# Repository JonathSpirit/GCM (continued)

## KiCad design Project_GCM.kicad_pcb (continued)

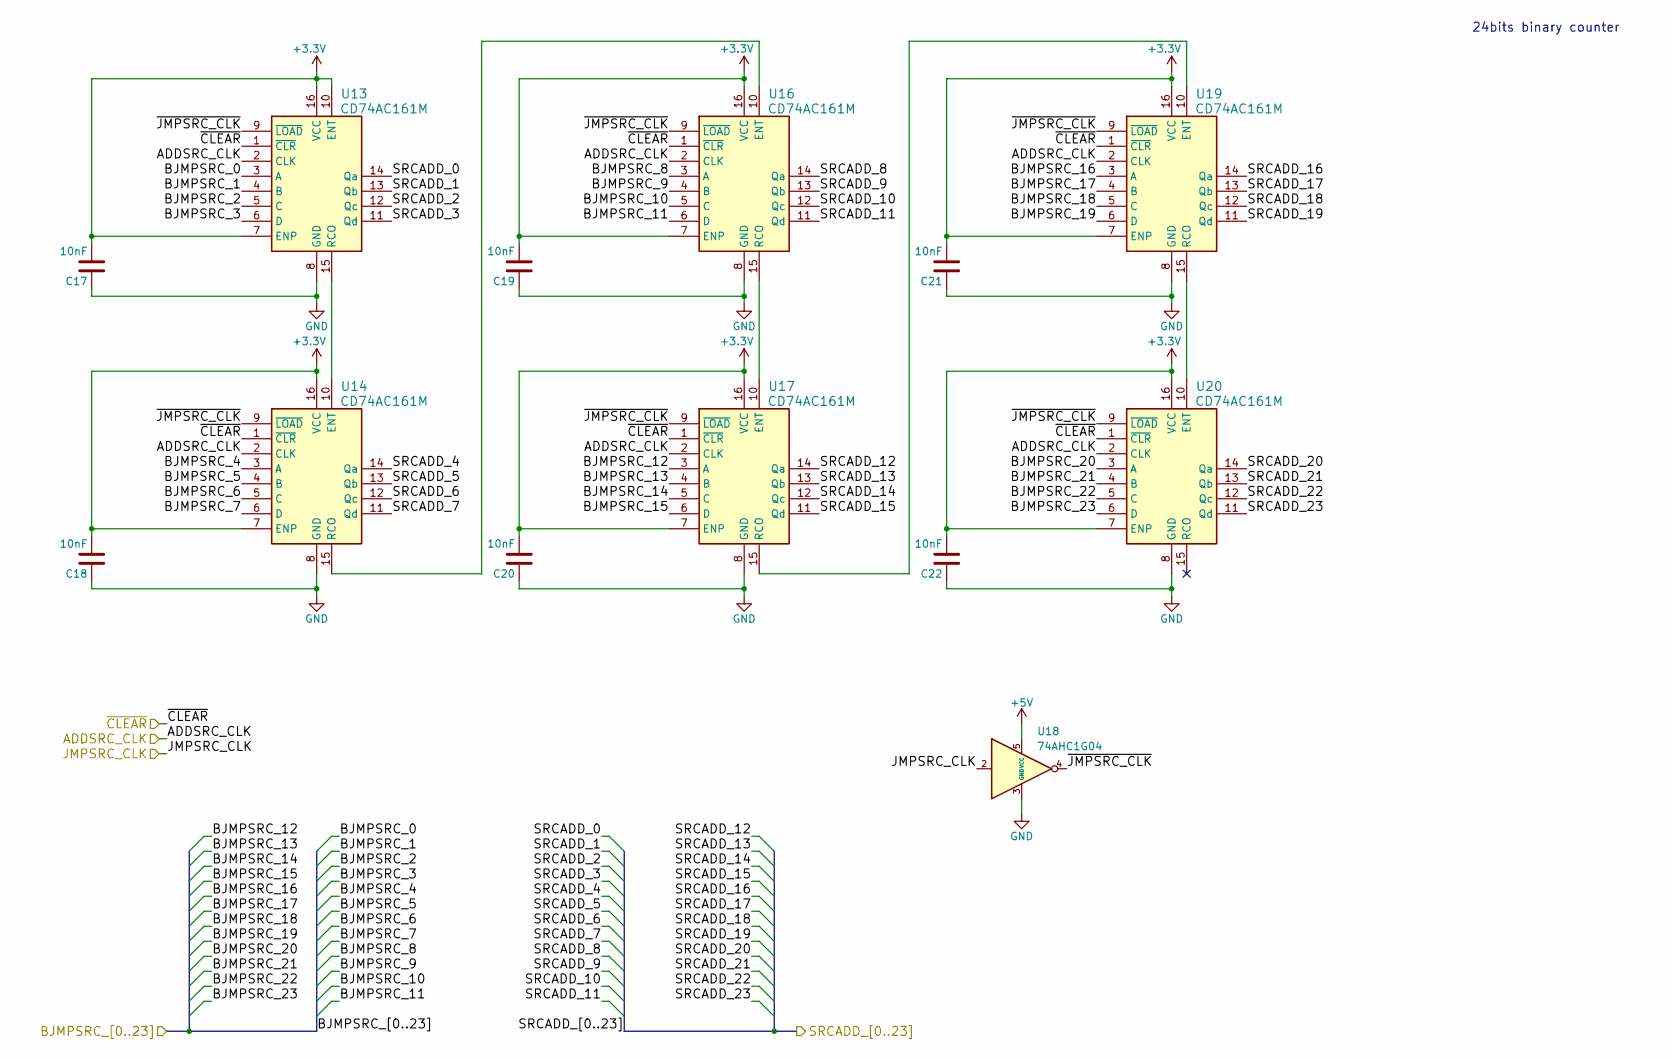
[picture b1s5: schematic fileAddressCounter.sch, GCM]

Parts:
C17, C18, C19, C20, C21, C22: 10nF; C_0805_2012Metric
U13, U14, U16, U17, U19, U20: CD74AC161M; SOP-16_3.9x9.9mm_P1.27mm
U18: 74AHC1G04; SOT-23-5

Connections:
+5V: U18.5 (VCC); also elsewhere on the board
/ADDSRC_CLK: U13.2 (CLK), U14.2 (CLK), U16.2 (CLK), U17.2 (CLK), U19.2 (CLK), U20.2 (CLK); also elsewhere on the board
/AddressCounter/BJMPSRC_0: U13.3 (A); also elsewhere on the board
/AddressCounter/BJMPSRC_1: U13.4 (B); also elsewhere on the board
/AddressCounter/BJMPSRC_2: U13.5 (C); also elsewhere on the board
/AddressCounter/BJMPSRC_3: U13.6 (D); also elsewhere on the board
/AddressCounter/BJMPSRC_4: U14.3 (A); also elsewhere on the board
/AddressCounter/BJMPSRC_5: U14.4 (B); also elsewhere on the board
/AddressCounter/BJMPSRC_6: U14.5 (C); also elsewhere on the board
/AddressCounter/BJMPSRC_7: U14.6 (D); also elsewhere on the board
/AddressCounter/BJMPSRC_8: U16.3 (A); also elsewhere on the board
/AddressCounter/BJMPSRC_9: U16.4 (B); also elsewhere on the board
/AddressCounter/BJMPSRC_10: U16.5 (C); also elsewhere on the board
/AddressCounter/BJMPSRC_11: U16.6 (D); also elsewhere on the board
/AddressCounter/BJMPSRC_12: U17.3 (A); also elsewhere on the board
/AddressCounter/BJMPSRC_13: U17.4 (B); also elsewhere on the board
/AddressCounter/BJMPSRC_14: U17.5 (C); also elsewhere on the board
/AddressCounter/BJMPSRC_15: U17.6 (D); also elsewhere on the board
/AddressCounter/BJMPSRC_16: U19.3 (A); also elsewhere on the board
/AddressCounter/BJMPSRC_17: U19.4 (B); also elsewhere on the board
/AddressCounter/BJMPSRC_18: U19.5 (C); also elsewhere on the board
/AddressCounter/BJMPSRC_19: U19.6 (D); also elsewhere on the board
/AddressCounter/BJMPSRC_20: U20.3 (A); also elsewhere on the board
/AddressCounter/BJMPSRC_21: U20.4 (B); also elsewhere on the board
/AddressCounter/BJMPSRC_22: U20.5 (C); also elsewhere on the board
/AddressCounter/BJMPSRC_23: U20.6 (D); also elsewhere on the board
/AddressCounter/~JMPSRC_CLK: U13.9 (~LOAD), U14.9 (~LOAD), U16.9 (~LOAD), U17.9 (~LOAD), U18.4, U19.9 (~LOAD), U20.9 (~LOAD)
/JMPSRC_CLK: U18.2; also elsewhere on the board
/SRCADD_0: U13.14 (Qa); also elsewhere on the board
/SRCADD_1: U13.13 (Qb); also elsewhere on the board
/SRCADD_2: U13.12 (Qc); also elsewhere on the board
/SRCADD_3: U13.11 (Qd); also elsewhere on the board
/SRCADD_4: U14.14 (Qa); also elsewhere on the board
/SRCADD_5: U14.13 (Qb); also elsewhere on the board
/SRCADD_6: U14.12 (Qc); also elsewhere on the board
/SRCADD_7: U14.11 (Qd); also elsewhere on the board
/SRCADD_8: U16.14 (Qa); also elsewhere on the board
/SRCADD_9: U16.13 (Qb); also elsewhere on the board
/SRCADD_10: U16.12 (Qc); also elsewhere on the board
/SRCADD_11: U16.11 (Qd); also elsewhere on the board
/SRCADD_12: U17.14 (Qa); also elsewhere on the board
/SRCADD_13: U17.13 (Qb); also elsewhere on the board
/SRCADD_14: U17.12 (Qc); also elsewhere on the board
/SRCADD_15: U17.11 (Qd); also elsewhere on the board
/SRCADD_16: U19.14 (Qa); also elsewhere on the board
/SRCADD_17: U19.13 (Qb); also elsewhere on the board
/SRCADD_18: U19.12 (Qc); also elsewhere on the board
/SRCADD_19: U19.11 (Qd); also elsewhere on the board
/SRCADD_20: U20.14 (Qa); also elsewhere on the board
/SRCADD_21: U20.13 (Qb); also elsewhere on the board
/SRCADD_22: U20.12 (Qc); also elsewhere on the board
/SRCADD_23: U20.11 (Qd); also elsewhere on the board
/~GLOBAL_RESET: U13.1 (~CLR), U14.1 (~CLR), U16.1 (~CLR), U17.1 (~CLR), U19.1 (~CLR), U20.1 (~CLR); also elsewhere on the board
GND: C17.1, C18.1, C19.1, C20.1, C21.1, C22.1, U13.8 (GND), U14.8 (GND), U16.8 (GND), U17.8 (GND), U18.3 (GND), U19.8 (GND), U20.8 (GND); also elsewhere on the board
unnamed: U13.15 (RCO), U14.10 (ENT)
unnamed: U14.15 (RCO), U16.10 (ENT)
unnamed: U16.15 (RCO), U17.10 (ENT)
unnamed: U17.15 (RCO), U19.10 (ENT)
unnamed: U19.15 (RCO), U20.10 (ENT)

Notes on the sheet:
24bits binary counter

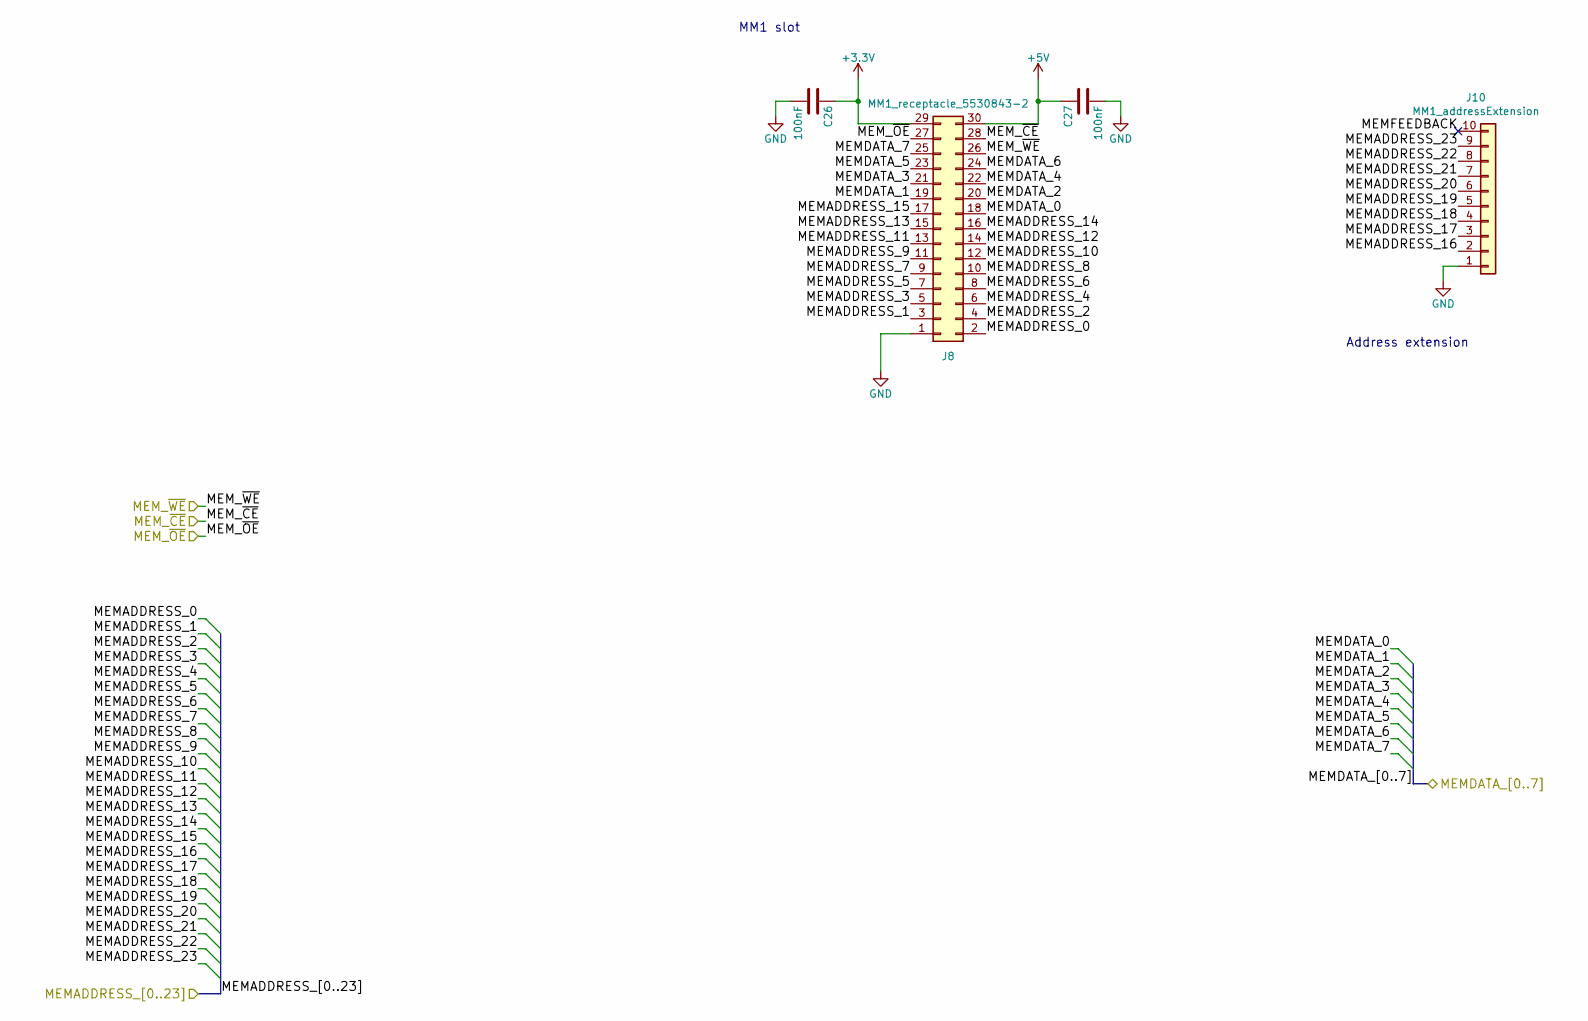
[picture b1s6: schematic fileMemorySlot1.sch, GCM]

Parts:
C26, C27: 100nF; C_0805_2012Metric
J8: MM1_receptacle_5530843-2; TE_5530843-2
J10: MM1_addressExtension; IDC-Header_2x05_P2.54mm_Vertical

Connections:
+5V: C27.1, J8.30; also elsewhere on the board
/MEM1_~CE: J8.28; also elsewhere on the board
/MEM1_~OE: J8.27; also elsewhere on the board
/MEM1_~WE: J8.26; also elsewhere on the board
/MemoryController/MEM1DATA_0: J8.18; also elsewhere on the board
/MemoryController/MEM1DATA_1: J8.19; also elsewhere on the board
/MemoryController/MEM1DATA_2: J8.20; also elsewhere on the board
/MemoryController/MEM1DATA_3: J8.21; also elsewhere on the board
/MemoryController/MEM1DATA_4: J8.22; also elsewhere on the board
/MemoryController/MEM1DATA_5: J8.23; also elsewhere on the board
/MemoryController/MEM1DATA_6: J8.24; also elsewhere on the board
/MemoryController/MEM1DATA_7: J8.25; also elsewhere on the board
/MemorySlot1/MEMADDRESS_0: J8.2; also elsewhere on the board
/MemorySlot1/MEMADDRESS_1: J8.3; also elsewhere on the board
/MemorySlot1/MEMADDRESS_2: J8.4; also elsewhere on the board
/MemorySlot1/MEMADDRESS_3: J8.5; also elsewhere on the board
/MemorySlot1/MEMADDRESS_4: J8.6; also elsewhere on the board
/MemorySlot1/MEMADDRESS_5: J8.7; also elsewhere on the board
/MemorySlot1/MEMADDRESS_6: J8.8; also elsewhere on the board
/MemorySlot1/MEMADDRESS_7: J8.9; also elsewhere on the board
/MemorySlot1/MEMADDRESS_8: J8.10; also elsewhere on the board
/MemorySlot1/MEMADDRESS_9: J8.11; also elsewhere on the board
/MemorySlot1/MEMADDRESS_10: J8.12; also elsewhere on the board
/MemorySlot1/MEMADDRESS_11: J8.13; also elsewhere on the board
/MemorySlot1/MEMADDRESS_12: J8.14; also elsewhere on the board
/MemorySlot1/MEMADDRESS_13: J8.15; also elsewhere on the board
/MemorySlot1/MEMADDRESS_14: J8.16; also elsewhere on the board
/MemorySlot1/MEMADDRESS_15: J8.17; also elsewhere on the board
/MemorySlot1/MEMADDRESS_16: J10.2; also elsewhere on the board
/MemorySlot1/MEMADDRESS_17: J10.3; also elsewhere on the board
/MemorySlot1/MEMADDRESS_18: J10.4; also elsewhere on the board
/MemorySlot1/MEMADDRESS_19: J10.5; also elsewhere on the board
/MemorySlot1/MEMADDRESS_20: J10.6; also elsewhere on the board
/MemorySlot1/MEMADDRESS_21: J10.7; also elsewhere on the board
/MemorySlot1/MEMADDRESS_22: J10.8; also elsewhere on the board
/MemorySlot1/MEMADDRESS_23: J10.9; also elsewhere on the board
/MemorySlot1/MEMFEEDBACK: J10.10
GND: C26.2, C27.2, J8.1, J10.1; also elsewhere on the board

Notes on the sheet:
Address extension
MM1 slot

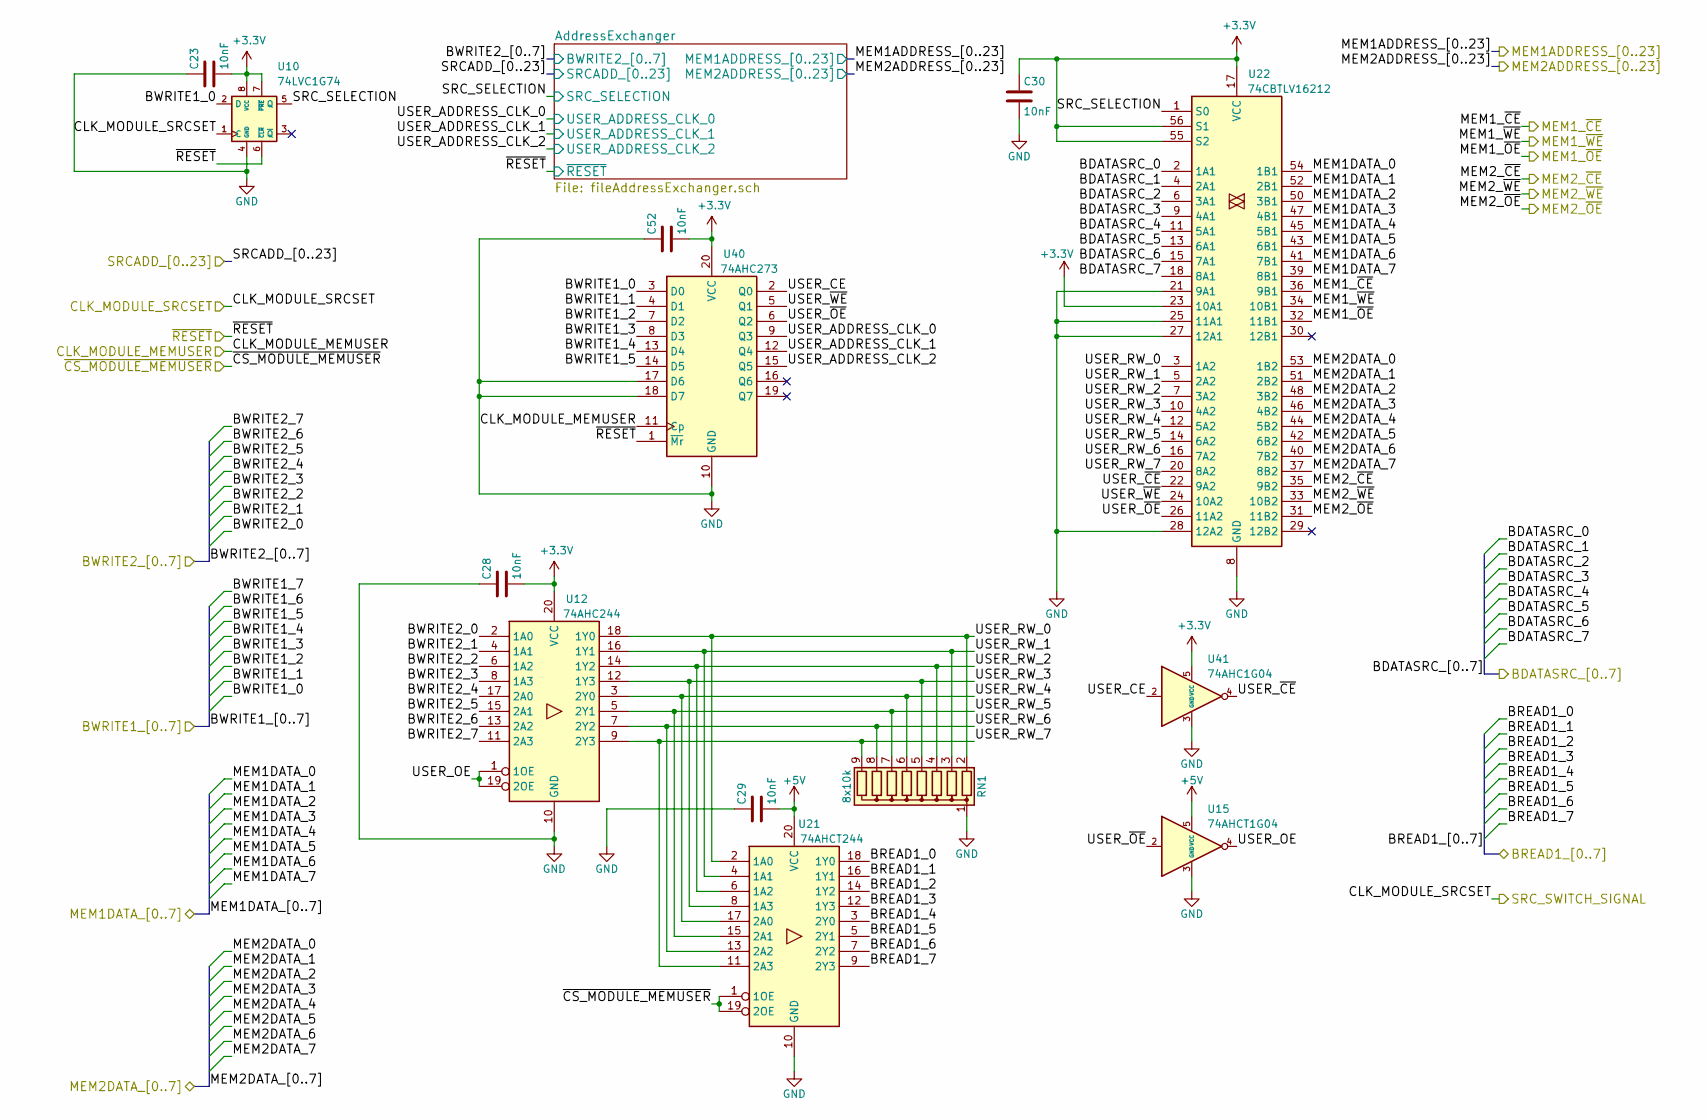
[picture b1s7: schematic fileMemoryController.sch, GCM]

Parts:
C23, C28, C29, C30, C52: 10nF; C_0805_2012Metric
RN1: 8x10k; R_Array_SIP9
U10: 74LVC1G74; SSOP-8_2.95x2.8mm_P0.65mm
U12: 74AHC244; SOIC-20W_7.5x12.8mm_P1.27mm
U15: 74AHCT1G04; SOT-23-5
U21: 74AHCT244; SOIC-20W_7.5x12.8mm_P1.27mm
U22: 74CBTLV16212; TSSOP-56_6.1x14mm_P0.5mm
U40: 74AHC273; SOIC-20W_7.5x12.8mm_P1.27mm
U41: 74AHC1G04; SOT-23-5

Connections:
+5V: C29.2, U15.5 (VCC), U21.20 (VCC); also elsewhere on the board
/BDATASRC_0: U22.2 (1A1); also elsewhere on the board
/BDATASRC_1: U22.4 (2A1); also elsewhere on the board
/BDATASRC_2: U22.6 (3A1); also elsewhere on the board
/BDATASRC_3: U22.9 (4A1); also elsewhere on the board
/BDATASRC_4: U22.11 (5A1); also elsewhere on the board
/BDATASRC_5: U22.13 (6A1); also elsewhere on the board
/BDATASRC_6: U22.15 (7A1); also elsewhere on the board
/BDATASRC_7: U22.18 (8A1); also elsewhere on the board
/CLK_MODULE_5: U40.11 (Cp); also elsewhere on the board
/CLK_MODULE_6: U10.1 (C); also elsewhere on the board
/ClockGenerator/BWRITE1_0: U10.2 (D), U40.3 (D0); also elsewhere on the board
/ClockGenerator/BWRITE1_1: U40.4 (D1); also elsewhere on the board
/ClockGenerator/BWRITE1_2: U40.7 (D2); also elsewhere on the board
/ClockGenerator/BWRITE1_3: U40.8 (D3); also elsewhere on the board
/ClockGenerator/BWRITE1_4: U40.13 (D4); also elsewhere on the board
/ClockGenerator/BWRITE1_5: U40.14 (D5); also elsewhere on the board
/Connector/BREAD1_0: U21.18 (1Y0); also elsewhere on the board
/Connector/BREAD1_1: U21.16 (1Y1); also elsewhere on the board
/Connector/BREAD1_2: U21.14 (1Y2); also elsewhere on the board
/Connector/BREAD1_3: U21.12 (1Y3); also elsewhere on the board
/Connector/BREAD1_4: U21.3 (2Y0); also elsewhere on the board
/Connector/BREAD1_5: U21.5 (2Y1); also elsewhere on the board
/Connector/BREAD1_6: U21.7 (2Y2); also elsewhere on the board
/Connector/BREAD1_7: U21.9 (2Y3); also elsewhere on the board
/Connector/BWRITE2_0: U12.2 (1A0); also elsewhere on the board
/Connector/BWRITE2_1: U12.4 (1A1); also elsewhere on the board
/Connector/BWRITE2_2: U12.6 (1A2); also elsewhere on the board
/Connector/BWRITE2_3: U12.8 (1A3); also elsewhere on the board
/Connector/BWRITE2_4: U12.17 (2A0); also elsewhere on the board
/Connector/BWRITE2_5: U12.15 (2A1); also elsewhere on the board
/Connector/BWRITE2_6: U12.13 (2A2); also elsewhere on the board
/Connector/BWRITE2_7: U12.11 (2A3); also elsewhere on the board
/MEM1_~CE: U22.36 (9B1); also elsewhere on the board
/MEM1_~OE: U22.32 (11B1); also elsewhere on the board
/MEM1_~WE: U22.34 (10B1); also elsewhere on the board
/MEM2_~CE: U22.35 (9B2); also elsewhere on the board
/MEM2_~OE: U22.31 (11B2); also elsewhere on the board
/MEM2_~WE: U22.33 (10B2); also elsewhere on the board
/MemoryController/MEM1DATA_0: U22.54 (1B1); also elsewhere on the board
/MemoryController/MEM1DATA_1: U22.52 (2B1); also elsewhere on the board
/MemoryController/MEM1DATA_2: U22.50 (3B1); also elsewhere on the board
/MemoryController/MEM1DATA_3: U22.47 (4B1); also elsewhere on the board
/MemoryController/MEM1DATA_4: U22.45 (5B1); also elsewhere on the board
/MemoryController/MEM1DATA_5: U22.43 (6B1); also elsewhere on the board
/MemoryController/MEM1DATA_6: U22.41 (7B1); also elsewhere on the board
/MemoryController/MEM1DATA_7: U22.39 (8B1); also elsewhere on the board
/MemoryController/MEM2DATA_0: U22.53 (1B2); also elsewhere on the board
/MemoryController/MEM2DATA_1: U22.51 (2B2); also elsewhere on the board
/MemoryController/MEM2DATA_2: U22.48 (3B2); also elsewhere on the board
/MemoryController/MEM2DATA_3: U22.46 (4B2); also elsewhere on the board
/MemoryController/MEM2DATA_4: U22.44 (5B2); also elsewhere on the board
/MemoryController/MEM2DATA_5: U22.42 (6B2); also elsewhere on the board
/MemoryController/MEM2DATA_6: U22.40 (7B2); also elsewhere on the board
/MemoryController/MEM2DATA_7: U22.37 (8B2); also elsewhere on the board
/MemoryController/SRC_SELECTION: U10.5 (Q), U22.1 (S0); also elsewhere on the board
/MemoryController/USER_ADDRESS_CLK_0: U40.9 (Q3); also elsewhere on the board
/MemoryController/USER_ADDRESS_CLK_1: U40.12 (Q4); also elsewhere on the board
/MemoryController/USER_ADDRESS_CLK_2: U40.15 (Q5); also elsewhere on the board
/MemoryController/USER_CE: U40.2 (Q0), U41.2
/MemoryController/USER_OE: U12.1 (1OE), U12.19 (2OE), U15.4
/MemoryController/USER_RW_0: RN1.2 (R1), U12.18 (1Y0), U21.2 (1A0), U22.3 (1A2)
/MemoryController/USER_RW_1: RN1.3 (R2), U12.16 (1Y1), U21.4 (1A1), U22.5 (2A2)
/MemoryController/USER_RW_2: RN1.4 (R3), U12.14 (1Y2), U21.6 (1A2), U22.7 (3A2)
/MemoryController/USER_RW_3: RN1.5 (R4), U12.12 (1Y3), U21.8 (1A3), U22.10 (4A2)
/MemoryController/USER_RW_4: RN1.6 (R5), U12.3 (2Y0), U21.17 (2A0), U22.12 (5A2)
/MemoryController/USER_RW_5: RN1.7 (R6), U12.5 (2Y1), U21.15 (2A1), U22.14 (6A2)
/MemoryController/USER_RW_6: RN1.8 (R7), U12.7 (2Y2), U21.13 (2A2), U22.16 (7A2)
/MemoryController/USER_RW_7: RN1.9 (R8), U12.9 (2Y3), U21.11 (2A3), U22.20 (8A2)
/MemoryController/USER_~CE: U22.22 (9A2), U41.4
/MemoryController/USER_~OE: U15.2, U22.26 (11A2), U40.6 (Q2)
/MemoryController/USER_~WE: U22.24 (10A2), U40.5 (Q1)
/~CS_MODULE_5: U21.1 (1OE), U21.19 (2OE); also elsewhere on the board
/~POWER_RESET: U10.6 (~CLR), U40.1 (~Mr); also elsewhere on the board
GND: C23.1, C28.1, C29.1, C30.2, C52.1, RN1.1 (common), U10.4 (GND), U12.10 (GND), U15.3 (GND), U21.10 (GND), U22.8 (GND), U22.19 (GND), U22.21 (9A1), U22.25 (11A1), U22.27 (12A1), U22.28 (12A2), U22.38 (GND), U22.49 (GND), U40.10 (GND), U40.17 (D6), U40.18 (D7), U41.3 (GND); also elsewhere on the board

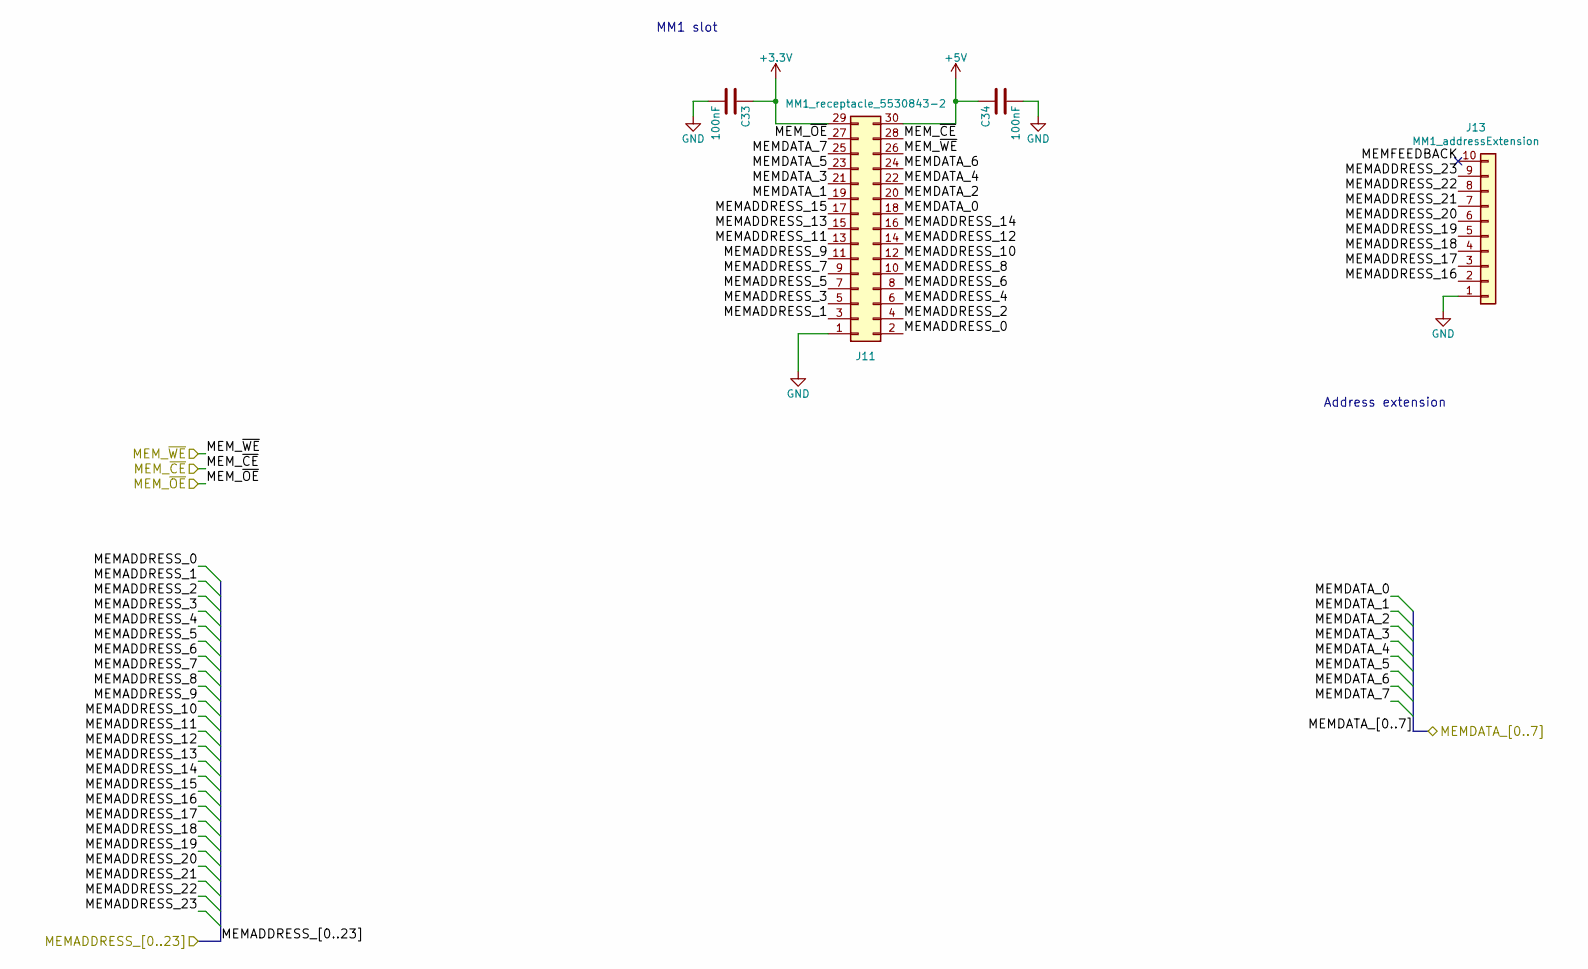
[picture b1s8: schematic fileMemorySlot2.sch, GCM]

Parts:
C26, C27: 100nF; C_0805_2012Metric
J8: MM1_receptacle_5530843-2; TE_5530843-2
J13: MM1_addressExtension; IDC-Header_2x05_P2.54mm_Vertical

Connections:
+5V: C27.1, J8.30; also elsewhere on the board
/MEM1_~CE: J8.28; also elsewhere on the board
/MEM1_~OE: J8.27; also elsewhere on the board
/MEM1_~WE: J8.26; also elsewhere on the board
/MemoryController/MEM1DATA_0: J8.18; also elsewhere on the board
/MemoryController/MEM1DATA_1: J8.19; also elsewhere on the board
/MemoryController/MEM1DATA_2: J8.20; also elsewhere on the board
/MemoryController/MEM1DATA_3: J8.21; also elsewhere on the board
/MemoryController/MEM1DATA_4: J8.22; also elsewhere on the board
/MemoryController/MEM1DATA_5: J8.23; also elsewhere on the board
/MemoryController/MEM1DATA_6: J8.24; also elsewhere on the board
/MemoryController/MEM1DATA_7: J8.25; also elsewhere on the board
/MemorySlot1/MEMADDRESS_0: J8.2; also elsewhere on the board
/MemorySlot1/MEMADDRESS_1: J8.3; also elsewhere on the board
/MemorySlot1/MEMADDRESS_2: J8.4; also elsewhere on the board
/MemorySlot1/MEMADDRESS_3: J8.5; also elsewhere on the board
/MemorySlot1/MEMADDRESS_4: J8.6; also elsewhere on the board
/MemorySlot1/MEMADDRESS_5: J8.7; also elsewhere on the board
/MemorySlot1/MEMADDRESS_6: J8.8; also elsewhere on the board
/MemorySlot1/MEMADDRESS_7: J8.9; also elsewhere on the board
/MemorySlot1/MEMADDRESS_8: J8.10; also elsewhere on the board
/MemorySlot1/MEMADDRESS_9: J8.11; also elsewhere on the board
/MemorySlot1/MEMADDRESS_10: J8.12; also elsewhere on the board
/MemorySlot1/MEMADDRESS_11: J8.13; also elsewhere on the board
/MemorySlot1/MEMADDRESS_12: J8.14; also elsewhere on the board
/MemorySlot1/MEMADDRESS_13: J8.15; also elsewhere on the board
/MemorySlot1/MEMADDRESS_14: J8.16; also elsewhere on the board
/MemorySlot1/MEMADDRESS_15: J8.17; also elsewhere on the board
/MemorySlot2/MEMADDRESS_16: J13.2; also elsewhere on the board
/MemorySlot2/MEMADDRESS_17: J13.3; also elsewhere on the board
/MemorySlot2/MEMADDRESS_18: J13.4; also elsewhere on the board
/MemorySlot2/MEMADDRESS_19: J13.5; also elsewhere on the board
/MemorySlot2/MEMADDRESS_20: J13.6; also elsewhere on the board
/MemorySlot2/MEMADDRESS_21: J13.7; also elsewhere on the board
/MemorySlot2/MEMADDRESS_22: J13.8; also elsewhere on the board
/MemorySlot2/MEMADDRESS_23: J13.9; also elsewhere on the board
/MemorySlot2/MEMFEEDBACK: J13.10
GND: C26.2, C27.2, J8.1, J13.1; also elsewhere on the board

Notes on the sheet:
Address extension
MM1 slot

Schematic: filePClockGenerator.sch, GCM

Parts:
C38, C39, C40, C41, C49, C50: 10nF; C_0805_2012Metric
U32: 74AHC273; SOIC-20W_7.5x12.8mm_P1.27mm
U33, U34: SN74LV393A; SOIC-14_3.9x8.7mm_P1.27mm
U35, U36, U37: CD74AC151; SOP-16_3.9x9.9mm_P1.27mm

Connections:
+5V: C38.2, C39.2, C40.2, C41.2, C49.2, C50.2, U32.20 (VCC), U33.14 (Vcc), U34.14 (Vcc), U35.16 (VCC), U36.16 (VCC), U37.16 (VCC); also elsewhere on the board
/CLK_MODULE_8: U32.11 (Cp); also elsewhere on the board
/ClockGenerator/BWRITE1_0: U32.3 (D0); also elsewhere on the board
/ClockGenerator/BWRITE1_1: U32.4 (D1); also elsewhere on the board
/ClockGenerator/BWRITE1_2: U32.7 (D2); also elsewhere on the board
/ClockGenerator/BWRITE1_3: U32.8 (D3); also elsewhere on the board
/ClockGenerator/BWRITE1_4: U32.13 (D4); also elsewhere on the board
/ClockGenerator/BWRITE1_5: U32.14 (D5); also elsewhere on the board
/ClockGenerator/BWRITE1_6: U32.17 (D6); also elsewhere on the board
/ClockGenerator/BWRITE1_7: U32.18 (D7); also elsewhere on the board
/ClockGenerator/CLK_50MHZ: U33.1 (1~CLK), U37.2 (D2); also elsewhere on the board
/ClockGenerator/PClockGenerator/CLK_50d2MHZ: U33.3 (1QA), U35.12 (D7)
/ClockGenerator/PClockGenerator/CLK_50d4MHZ: U33.4 (1QB), U35.13 (D6)
/ClockGenerator/PClockGenerator/CLK_50d8MHZ: U33.5 (1QC), U35.14 (D5)
/ClockGenerator/PClockGenerator/CLK_50d16MHZ: U33.6 (1QD), U33.13 (2~CLK), U35.15 (D4)
/ClockGenerator/PClockGenerator/CLK_50d32MHZ: U33.11 (2QA), U35.1 (D3)
/ClockGenerator/PClockGenerator/CLK_50d64MHZ: U33.10 (2QB), U35.2 (D2)
/ClockGenerator/PClockGenerator/CLK_50d128MHZ: U33.9 (2QC), U35.3 (D1)
/ClockGenerator/PClockGenerator/CLK_50d256MHZ: U33.8 (2QD), U34.1 (1~CLK), U35.4 (D0)
/ClockGenerator/PClockGenerator/CLK_50d512MHZ: U34.3 (1QA), U36.12 (D7)
/ClockGenerator/PClockGenerator/CLK_50d1024MHZ: U34.4 (1QB), U36.13 (D6)
/ClockGenerator/PClockGenerator/CLK_50d2048MHZ: U34.5 (1QC), U36.14 (D5)
/ClockGenerator/PClockGenerator/CLK_50d4096MHZ: U34.6 (1QD), U34.13 (2~CLK), U36.15 (D4)
/ClockGenerator/PClockGenerator/CLK_50d8192MHZ: U34.11 (2QA), U36.1 (D3)
/ClockGenerator/PClockGenerator/CLK_50d16384MHZ: U34.10 (2QB), U36.2 (D2)
/ClockGenerator/PClockGenerator/CLK_50d32768MHZ: U34.9 (2QC), U36.3 (D1)
/ClockGenerator/PClockGenerator/CLK_50d65536MHZ: U34.8 (2QD), U36.4 (D0)
/ClockGenerator/PClockGenerator/CLK_OUT_FAST: U35.5 (Y), U37.3 (D1)
/ClockGenerator/PClockGenerator/CLK_OUT_SLOW: U36.5 (Y), U37.4 (D0)
/ClockGenerator/PClockGenerator/CLK_SELECT_0: U32.16 (Q6), U37.11 (A)
/ClockGenerator/PClockGenerator/CLK_SELECT_1: U32.19 (Q7), U37.10 (B)
/ClockGenerator/PClockGenerator/CLK_SELECT_FAST_0: U32.2 (Q0), U35.11 (A)
/ClockGenerator/PClockGenerator/CLK_SELECT_FAST_1: U32.5 (Q1), U35.10 (B)
/ClockGenerator/PClockGenerator/CLK_SELECT_FAST_2: U32.6 (Q2), U35.9 (C)
/ClockGenerator/PClockGenerator/CLK_SELECT_SLOW_0: U32.9 (Q3), U36.11 (A)
/ClockGenerator/PClockGenerator/CLK_SELECT_SLOW_1: U32.12 (Q4), U36.10 (B)
/ClockGenerator/PClockGenerator/CLK_SELECT_SLOW_2: U32.15 (Q5), U36.9 (C)
/P_CLK: U37.5 (Y); also elsewhere on the board
/~POWER_RESET: U32.1 (~Mr); also elsewhere on the board
GND: C38.1, C39.1, C40.1, C41.1, C49.1, C50.1, U32.10 (GND), U33.2 (1CLR), U33.7 (GND), U33.12 (2CLR), U34.2 (1CLR), U34.7 (GND), U34.12 (2CLR), U35.7 (~G), U35.8 (GND), U36.7 (~G), U36.8 (GND), U37.1 (D3), U37.7 (~G), U37.8 (GND), U37.9 (C), U37.12 (D7), U37.13 (D6), U37.14 (D5), U37.15 (D4); also elsewhere on the board

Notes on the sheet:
Peripheral clock generation

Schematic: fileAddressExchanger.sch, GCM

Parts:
C31, C32, C53, C54, C55: 10nF; C_0805_2012Metric
U23, U24: 74CBTLV16212; TSSOP-56_6.1x14mm_P0.5mm
U42, U43, U44: 74AHC273; SOIC-20W_7.5x12.8mm_P1.27mm

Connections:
/Connector/BWRITE2_0: U42.3 (D0), U43.3 (D0), U44.3 (D0); also elsewhere on the board
/Connector/BWRITE2_1: U42.4 (D1), U43.4 (D1), U44.4 (D1); also elsewhere on the board
/Connector/BWRITE2_2: U42.7 (D2), U43.7 (D2), U44.7 (D2); also elsewhere on the board
/Connector/BWRITE2_3: U42.8 (D3), U43.8 (D3), U44.8 (D3); also elsewhere on the board
/Connector/BWRITE2_4: U42.13 (D4), U43.13 (D4), U44.13 (D4); also elsewhere on the board
/Connector/BWRITE2_5: U42.14 (D5), U43.14 (D5), U44.14 (D5); also elsewhere on the board
/Connector/BWRITE2_6: U42.17 (D6), U43.17 (D6), U44.17 (D6); also elsewhere on the board
/Connector/BWRITE2_7: U42.18 (D7), U43.18 (D7), U44.18 (D7); also elsewhere on the board
/MemoryController/AddressExchanger/USERADDRESS_0: U23.3 (1A2), U42.2 (Q0)
/MemoryController/AddressExchanger/USERADDRESS_1: U23.5 (2A2), U42.5 (Q1)
/MemoryController/AddressExchanger/USERADDRESS_2: U23.7 (3A2), U42.6 (Q2)
/MemoryController/AddressExchanger/USERADDRESS_3: U23.10 (4A2), U42.9 (Q3)
/MemoryController/AddressExchanger/USERADDRESS_4: U23.12 (5A2), U42.12 (Q4)
/MemoryController/AddressExchanger/USERADDRESS_5: U23.14 (6A2), U42.15 (Q5)
/MemoryController/AddressExchanger/USERADDRESS_6: U23.16 (7A2), U42.16 (Q6)
/MemoryController/AddressExchanger/USERADDRESS_7: U23.20 (8A2), U42.19 (Q7)
/MemoryController/AddressExchanger/USERADDRESS_8: U23.22 (9A2), U43.2 (Q0)
/MemoryController/AddressExchanger/USERADDRESS_9: U23.24 (10A2), U43.5 (Q1)
/MemoryController/AddressExchanger/USERADDRESS_10: U23.26 (11A2), U43.6 (Q2)
/MemoryController/AddressExchanger/USERADDRESS_11: U23.28 (12A2), U43.9 (Q3)
/MemoryController/AddressExchanger/USERADDRESS_12: U24.3 (1A2), U43.12 (Q4)
/MemoryController/AddressExchanger/USERADDRESS_13: U24.5 (2A2), U43.15 (Q5)
/MemoryController/AddressExchanger/USERADDRESS_14: U24.7 (3A2), U43.16 (Q6)
/MemoryController/AddressExchanger/USERADDRESS_15: U24.10 (4A2), U43.19 (Q7)
/MemoryController/AddressExchanger/USERADDRESS_16: U24.12 (5A2), U44.2 (Q0)
/MemoryController/AddressExchanger/USERADDRESS_17: U24.14 (6A2), U44.5 (Q1)
/MemoryController/AddressExchanger/USERADDRESS_18: U24.16 (7A2), U44.6 (Q2)
/MemoryController/AddressExchanger/USERADDRESS_19: U24.20 (8A2), U44.9 (Q3)
/MemoryController/AddressExchanger/USERADDRESS_20: U24.22 (9A2), U44.12 (Q4)
/MemoryController/AddressExchanger/USERADDRESS_21: U24.24 (10A2), U44.15 (Q5)
/MemoryController/AddressExchanger/USERADDRESS_22: U24.26 (11A2), U44.16 (Q6)
/MemoryController/AddressExchanger/USERADDRESS_23: U24.28 (12A2), U44.19 (Q7)
/MemoryController/SRC_SELECTION: U23.1 (S0), U24.1 (S0); also elsewhere on the board
/MemoryController/USER_ADDRESS_CLK_0: U42.11 (Cp); also elsewhere on the board
/MemoryController/USER_ADDRESS_CLK_1: U43.11 (Cp); also elsewhere on the board
/MemoryController/USER_ADDRESS_CLK_2: U44.11 (Cp); also elsewhere on the board
/MemorySlot1/MEMADDRESS_0: U23.54 (1B1); also elsewhere on the board
/MemorySlot1/MEMADDRESS_1: U23.52 (2B1); also elsewhere on the board
/MemorySlot1/MEMADDRESS_2: U23.50 (3B1); also elsewhere on the board
/MemorySlot1/MEMADDRESS_3: U23.47 (4B1); also elsewhere on the board
/MemorySlot1/MEMADDRESS_4: U23.45 (5B1); also elsewhere on the board
/MemorySlot1/MEMADDRESS_5: U23.43 (6B1); also elsewhere on the board
/MemorySlot1/MEMADDRESS_6: U23.41 (7B1); also elsewhere on the board
/MemorySlot1/MEMADDRESS_7: U23.39 (8B1); also elsewhere on the board
/MemorySlot1/MEMADDRESS_8: U23.36 (9B1); also elsewhere on the board
/MemorySlot1/MEMADDRESS_9: U23.34 (10B1); also elsewhere on the board
/MemorySlot1/MEMADDRESS_10: U23.32 (11B1); also elsewhere on the board
/MemorySlot1/MEMADDRESS_11: U23.30 (12B1); also elsewhere on the board
/MemorySlot1/MEMADDRESS_12: U24.54 (1B1); also elsewhere on the board
/MemorySlot1/MEMADDRESS_13: U24.52 (2B1); also elsewhere on the board
/MemorySlot1/MEMADDRESS_14: U24.50 (3B1); also elsewhere on the board
/MemorySlot1/MEMADDRESS_15: U24.47 (4B1); also elsewhere on the board
/MemorySlot1/MEMADDRESS_16: U24.45 (5B1); also elsewhere on the board
/MemorySlot1/MEMADDRESS_17: U24.43 (6B1); also elsewhere on the board
/MemorySlot1/MEMADDRESS_18: U24.41 (7B1); also elsewhere on the board
/MemorySlot1/MEMADDRESS_19: U24.39 (8B1); also elsewhere on the board
/MemorySlot1/MEMADDRESS_20: U24.36 (9B1); also elsewhere on the board
/MemorySlot1/MEMADDRESS_21: U24.34 (10B1); also elsewhere on the board
/MemorySlot1/MEMADDRESS_22: U24.32 (11B1); also elsewhere on the board
/MemorySlot1/MEMADDRESS_23: U24.30 (12B1); also elsewhere on the board
/MemorySlot2/MEMADDRESS_0: U23.53 (1B2); also elsewhere on the board
/MemorySlot2/MEMADDRESS_1: U23.51 (2B2); also elsewhere on the board
/MemorySlot2/MEMADDRESS_2: U23.48 (3B2); also elsewhere on the board
/MemorySlot2/MEMADDRESS_3: U23.46 (4B2); also elsewhere on the board
/MemorySlot2/MEMADDRESS_4: U23.44 (5B2); also elsewhere on the board
/MemorySlot2/MEMADDRESS_5: U23.42 (6B2); also elsewhere on the board
/MemorySlot2/MEMADDRESS_6: U23.40 (7B2); also elsewhere on the board
/MemorySlot2/MEMADDRESS_7: U23.37 (8B2); also elsewhere on the board
/MemorySlot2/MEMADDRESS_8: U23.35 (9B2); also elsewhere on the board
/MemorySlot2/MEMADDRESS_9: U23.33 (10B2); also elsewhere on the board
/MemorySlot2/MEMADDRESS_10: U23.31 (11B2); also elsewhere on the board
/MemorySlot2/MEMADDRESS_11: U23.29 (12B2); also elsewhere on the board
/MemorySlot2/MEMADDRESS_12: U24.53 (1B2); also elsewhere on the board
/MemorySlot2/MEMADDRESS_13: U24.51 (2B2); also elsewhere on the board
/MemorySlot2/MEMADDRESS_14: U24.48 (3B2); also elsewhere on the board
/MemorySlot2/MEMADDRESS_15: U24.46 (4B2); also elsewhere on the board
/MemorySlot2/MEMADDRESS_16: U24.44 (5B2); also elsewhere on the board
/MemorySlot2/MEMADDRESS_17: U24.42 (6B2); also elsewhere on the board
/MemorySlot2/MEMADDRESS_18: U24.40 (7B2); also elsewhere on the board
/MemorySlot2/MEMADDRESS_19: U24.37 (8B2); also elsewhere on the board
/MemorySlot2/MEMADDRESS_20: U24.35 (9B2); also elsewhere on the board
/MemorySlot2/MEMADDRESS_21: U24.33 (10B2); also elsewhere on the board
/MemorySlot2/MEMADDRESS_22: U24.31 (11B2); also elsewhere on the board
/MemorySlot2/MEMADDRESS_23: U24.29 (12B2); also elsewhere on the board
/SRCADD_0: U23.2 (1A1); also elsewhere on the board
/SRCADD_1: U23.4 (2A1); also elsewhere on the board
/SRCADD_2: U23.6 (3A1); also elsewhere on the board
/SRCADD_3: U23.9 (4A1); also elsewhere on the board
/SRCADD_4: U23.11 (5A1); also elsewhere on the board
/SRCADD_5: U23.13 (6A1); also elsewhere on the board
/SRCADD_6: U23.15 (7A1); also elsewhere on the board
/SRCADD_7: U23.18 (8A1); also elsewhere on the board
/SRCADD_8: U23.21 (9A1); also elsewhere on the board
/SRCADD_9: U23.23 (10A1); also elsewhere on the board
/SRCADD_10: U23.25 (11A1); also elsewhere on the board
/SRCADD_11: U23.27 (12A1); also elsewhere on the board
/SRCADD_12: U24.2 (1A1); also elsewhere on the board
/SRCADD_13: U24.4 (2A1); also elsewhere on the board
/SRCADD_14: U24.6 (3A1); also elsewhere on the board
/SRCADD_15: U24.9 (4A1); also elsewhere on the board
/SRCADD_16: U24.11 (5A1); also elsewhere on the board
/SRCADD_17: U24.13 (6A1); also elsewhere on the board
/SRCADD_18: U24.15 (7A1); also elsewhere on the board
/SRCADD_19: U24.18 (8A1); also elsewhere on the board
/SRCADD_20: U24.21 (9A1); also elsewhere on the board
/SRCADD_21: U24.23 (10A1); also elsewhere on the board
/SRCADD_22: U24.25 (11A1); also elsewhere on the board
/SRCADD_23: U24.27 (12A1); also elsewhere on the board
/~POWER_RESET: U42.1 (~Mr), U43.1 (~Mr), U44.1 (~Mr); also elsewhere on the board
GND: C31.2, C32.2, C53.1, C54.1, C55.1, U23.8 (GND), U23.19 (GND), U23.38 (GND), U23.49 (GND), U24.8 (GND), U24.19 (GND), U24.38 (GND), U24.49 (GND), U42.10 (GND), U43.10 (GND), U44.10 (GND); also elsewhere on the board

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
